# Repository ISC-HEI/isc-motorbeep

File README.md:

<picture>
  <source media="(prefers-color-scheme: dark)"
          srcset="https://raw.githubusercontent.com/ISC-HEI/isc-logos/main/white/ISC%20Logo%20inline%20white%20v3%20-%20large.webp">
  
</picture>

# ISC MotorBeep — ESP32 dual-stepper + audio board

A complete [KiCad 9](https://www.kicad.org/) schematic for an ESP32 board driving two bipolar
stepper motors and a small speaker, powered from 3× AA cells. It is an improved derivative of the
ESP32 DevKit DOIT v1: the AMS1117 LDO, the thin bulk capacitance, the micro-USB connector and the
absent battery sensing are all addressed.

## The brief

Take the [ESP32 DevKit DOIT v1](https://embedded-systems-design.github.io/overview-of-the-esp32-devkit-doit-v1/)
as the reference design and produce an improved version of it that drives **two stepper motors** and
a **small speaker**, running off **AA cells** — originally two, changed to three during the work.
Deliver the complete schematic in KiCad (installing it as needed), authored through the
[KiCAD-MCP-Server](https://github.com/mixelpixx/KiCAD-MCP-Server).

## What was built

1. KiCad 9 installed, the MCP server built, and patched — it emits the KiCad 10 file format, which 9 refuses to load.
2. Architecture chosen from the battery up: 3× AA (2.8–4.8 V) sits inside the STSPIN220 and MAX98357A supply windows, so motors and audio need no converter; only the ESP32 does, and it must be a buck-boost.
3. Parts picked against what KiCad actually ships — `DRV8834` and `TPS63020` have no stock symbols, so `STSPIN220` and `TPS63001` replaced them.
4. Four hierarchical sheets authored headlessly: power, MCU, motors, audio. **Root ERC: 0 errors.**
5. Verified three ways — ERC, a rendered image of every sheet reviewed by eye, and `check_nets.py`, which asserts 29 design-intent connections against the exported netlist.
6. Footprints assigned and checked to exist, netlist and PDF exported, BOM priced against the real JLCPCB catalog (**$14.49**, part links in [`doc/BOM.md`](./doc/BOM.md)).
7. A 4-layer PCB created and fully placed — antenna overhanging the edge, switching nodes 4.3 mm — then rendered in 3D. **Routing was not done.**

## Schematic

Four hierarchical sheets plus a root. Click any image for full resolution, or read
[the complete PDF](./doc/isc-motorbeep-schematic.pdf).

### Root — sheet hierarchy

### Power — 3× AA, Schottky OR, TPS63001 buck-boost, USB-C

### MCU — ESP32-WROOM-32E, CP2102N bridge, auto-reset

### Motors — 2× STSPIN220 stepper drivers

### Audio — MAX98357A Class-D

## PCB

Placed, not routed. 70 x 50 mm, 4 layers, 69 footprints, verified by
[`tools/place_board.py`](./tools/place_board.py): no overlaps, nothing off-board, and nothing
inside the ESP32 antenna keepout. The module's antenna deliberately overhangs the top edge, and
L1 sits directly left of the TPS63001 so both switching nodes come out as 4.3 mm straight runs.

Routing is not done, so there are no tracks and no copper pours yet.

## Architecture

Three AA cells deliver 2.8–4.8 V, and that range sits inside the supply window of both power loads —
the STSPIN220 works from 1.8 V and the MAX98357A from 2.5 V — so the motors and the speaker run
straight off the pack with no converter at all. Only the ESP32 needs one, and it has to be a
buck-boost: the pack starts above 3.3 V and ends below it, so an LDO would drop out and a plain
boost could not regulate down. USB and battery are OR'd through two Schottky diodes into that
converter only, which is what stops USB from back-feeding and charging the alkaline cells.

```mermaid
flowchart LR
    B["3x AA / 2.8-4.8 V"] --> D2["D2 Schottky"]
    U["USB-C 5 V"] --> D1["D1 Schottky"]
    D1 --> V["VSYS"]
    D2 --> V
    V --> R["U2 TPS63001 buck-boost"]
    R --> L3["+3V3 - ESP32 only"]
    B --> M["U5/U6 STSPIN220 - 2 steppers"]
    B --> A["U7 MAX98357A - speaker"]
```

Every line the ESP32 gates has a resistor defining its state at reset, so the motors cannot twitch
and the speaker cannot pop at power-up; `GPIO12` is left unconnected because it straps the flash
voltage. The reasoning, the full pin budget and the pre-fabrication checklist are in
**[`doc/DESIGN.md`](./doc/DESIGN.md)**.

## Bill of materials

70 components in 36 lines, about **$14.49** in parts at 1-off LCSC prices (catalog snapshot of
14 September 2026). Full priced BOM with a part link per line: **[`doc/BOM.md`](./doc/BOM.md)**.

> [!WARNING]
> **The STSPIN220 was down to 27 units at JLCPCB in that snapshot** — check it live before
> committing to a build. `doc/BOM.md` names the substitute and what swapping costs you.

Almost every part is a JLCPCB *Extended* part with a $3 setup fee each, so for a one-off, hand
assembly is cheaper than paying the setup fees.

## Open it

```bash
kicad hardware/isc-motorbeep/isc-motorbeep.kicad_pro
```

Generated headlessly through the KiCAD-MCP-Server — reproduction steps, the KiCad 9 file-format
patch it needs, and the helper scripts are in [`doc/TOOLING.md`](./doc/TOOLING.md).

## Before fabricating

The schematic is complete and ERC-clean, but two questions could not be settled without
manufacturer datasheets. Both are detailed, with the rest of the checklist, in
[`doc/DESIGN.md` §8.5–8.6](./doc/DESIGN.md):

- **Are the STSPIN220 and MAX98357A logic inputs rated independently of their supply?** The ESP32
  drives 3.3 V into them while `+BATT` may be at 2.8 V. If either is VS-referenced, the design
  breaks at low battery. This is the one that matters.
- **The QFN-16 exposed-pad dimension** for U5/U6/U7 — stock footprint variants run 1.45 to 1.85 mm,
  and it is the thermal path the current-chopping depends on.

---

## License

Copyright © 2026 P.-A. Mudry / ISC — HES-SO Valais. Released under
[CC-BY-NC-ND 4.0](https://creativecommons.org/licenses/by-nc-nd/4.0/).

---

*Made with ♥ by mui, 2026*

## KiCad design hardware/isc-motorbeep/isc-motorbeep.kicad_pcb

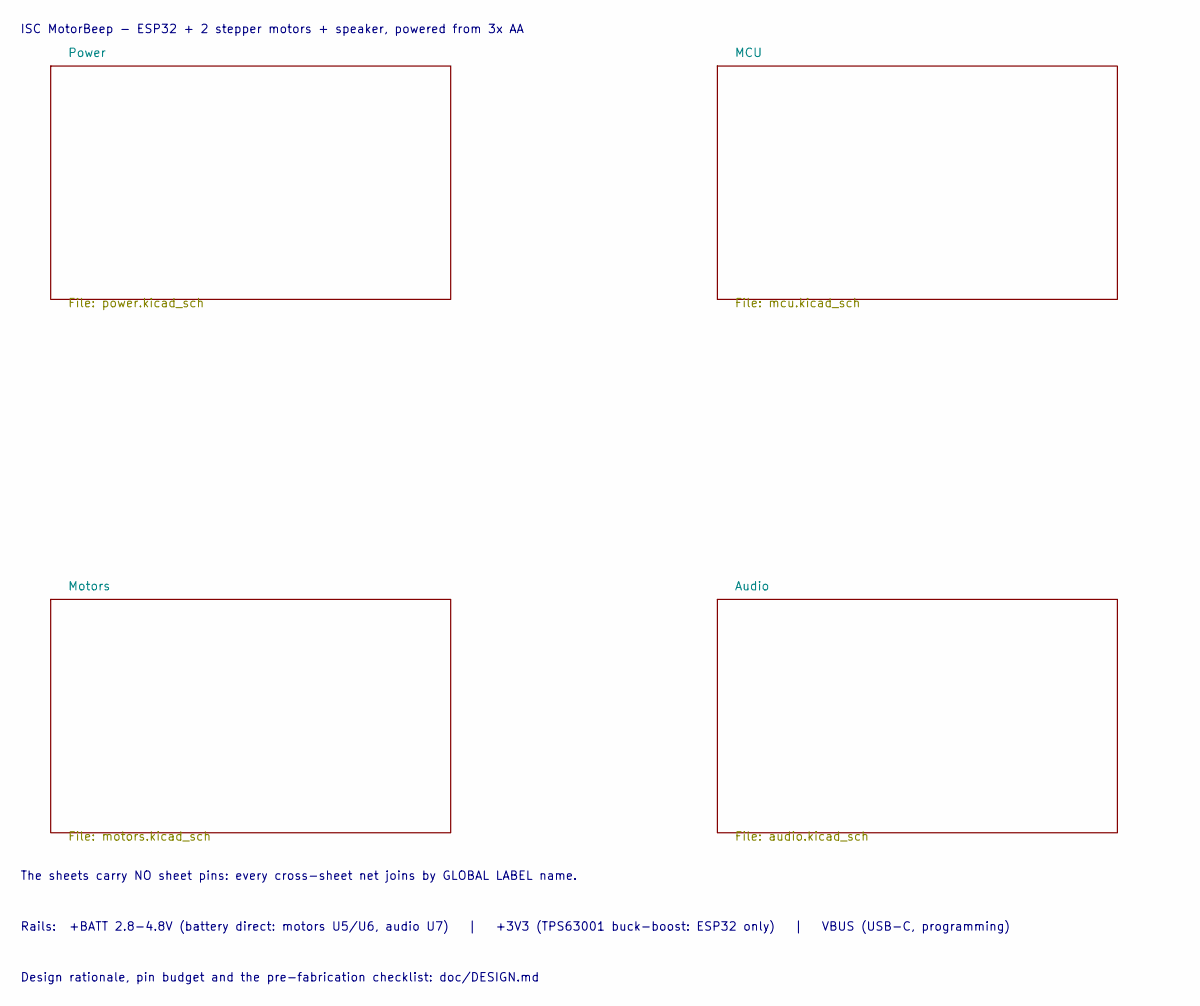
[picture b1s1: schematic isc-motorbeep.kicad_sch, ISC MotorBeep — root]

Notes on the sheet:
ISC MotorBeep - ESP32 + 2 stepper motors + speaker, powered from 3x AA
The sheets carry NO sheet pins: every cross-sheet net joins by GLOBAL LABEL name.
Rails: +BATT 2.8-4.8V (battery direct: motors U5/U6, audio U7) | +3V3 (TPS63001 buck-boost: ESP32 only) | VBUS (USB-C, programming)
Design rationale, pin budget and the pre-fabrication checklist: doc/DESIGN.md

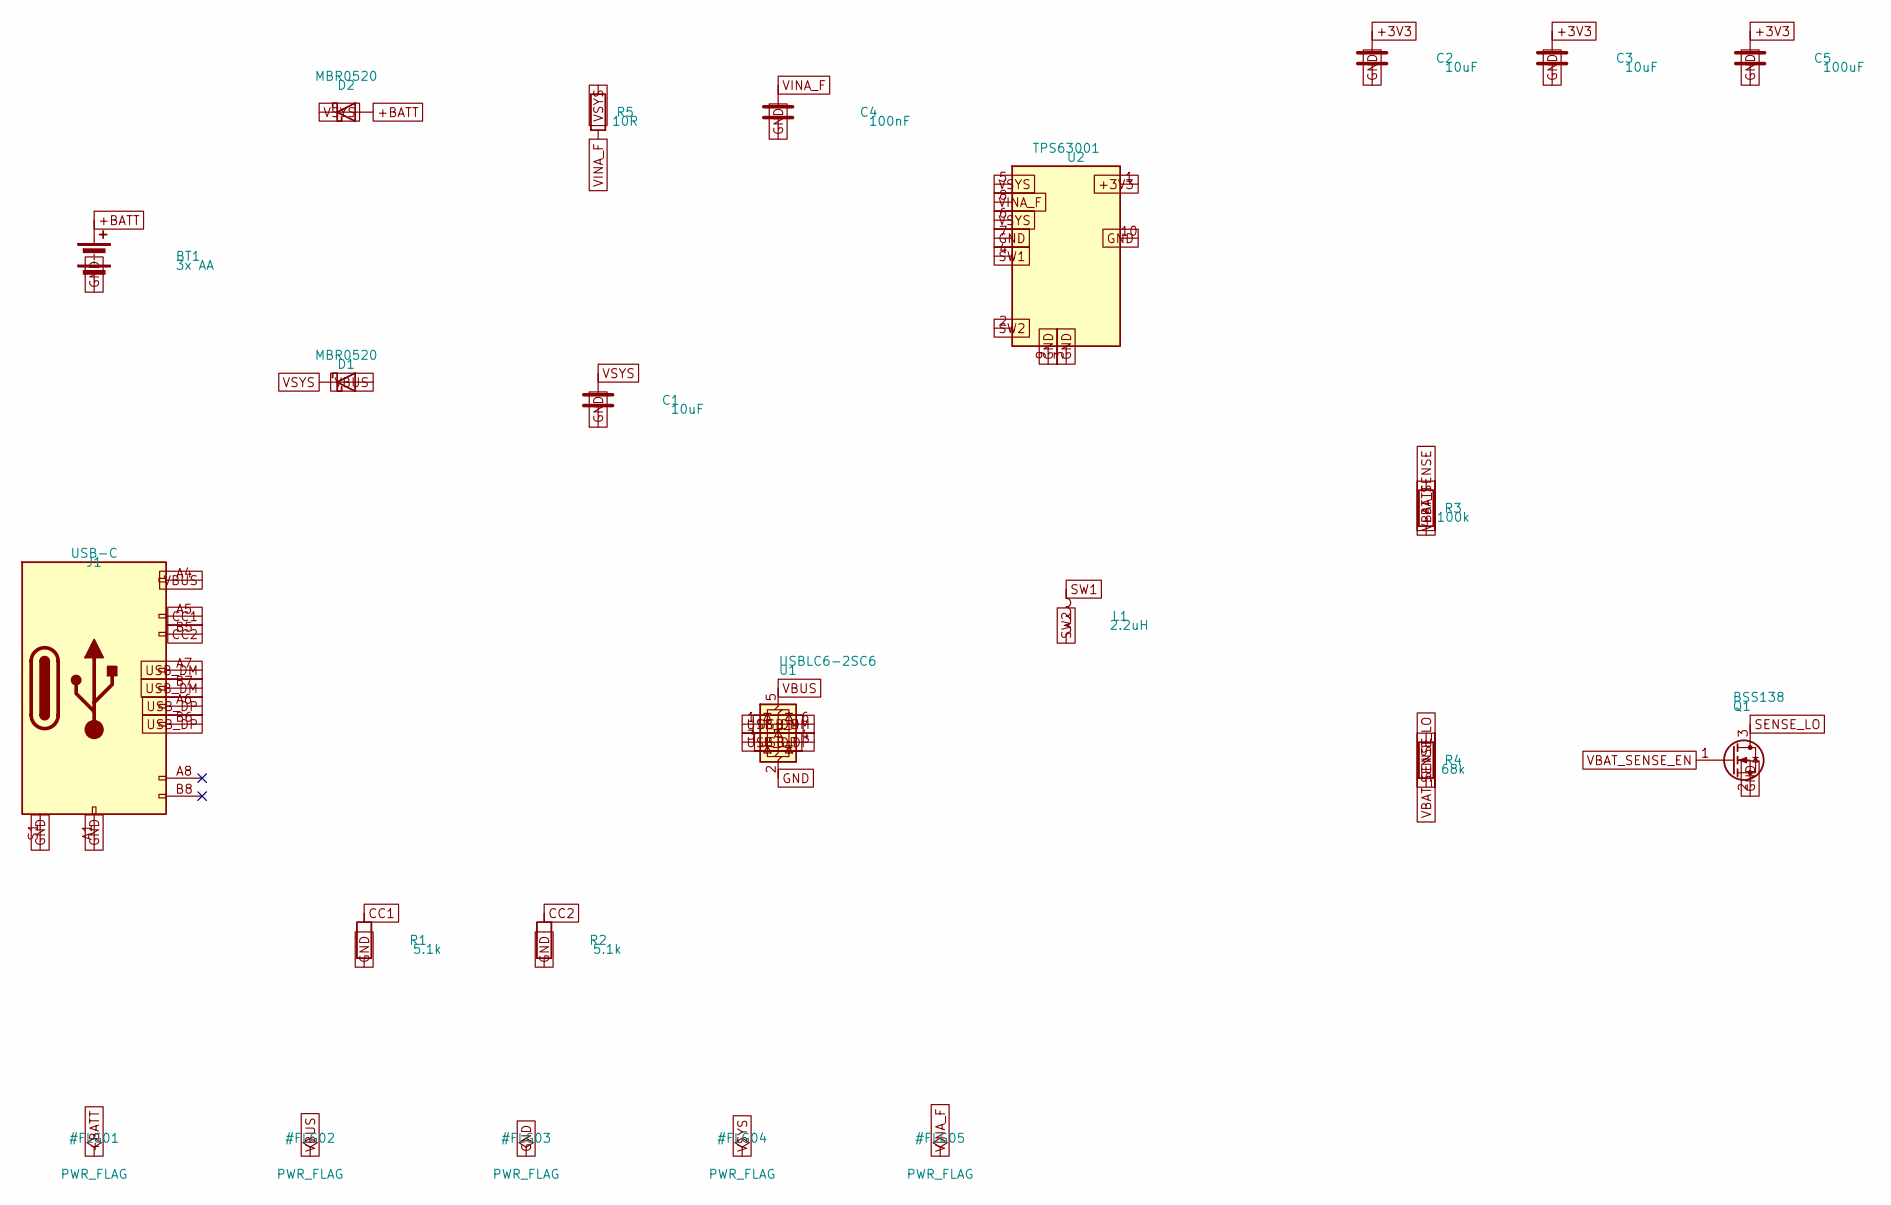
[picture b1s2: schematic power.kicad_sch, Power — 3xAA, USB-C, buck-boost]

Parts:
BT1: 3x AA; PinHeader_1x02_P2.54mm_Vertical
C1, C2, C3: 10uF; C_0805_2012Metric
C4: 100nF; C_0603_1608Metric
C5: 100uF; C_1210_3225Metric
D1, D2: MBR0520; D_SOD-123
J1: USB-C; USB_C_Receptacle_G-Switch_GT-USB-7010ASV
L1: 2.2uH; L_Bourns-SRN4018
Q1: BSS138; SOT-23
R1, R2: 5.1k; R_0603_1608Metric
R3: 100k; R_0603_1608Metric
R4: 68k; R_0603_1608Metric
R5: 10R; R_0603_1608Metric
U1: USBLC6-2SC6; SOT-23-6
U2: TPS63001; Texas_DRC0010J_ThermalVias

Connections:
+3V3: C2.1, C3.1, C5.1, U2.1 (VOUT); also elsewhere on the board
+BATT: BT1.1 (+), D2.2 (A), R3.1; also elsewhere on the board
CC1: J1.A5 (CC1), R1.1
CC2: J1.B5 (CC2), R2.1
GND: BT1.2 (-), C1.2, C2.2, C3.2, C4.2, C5.2, J1.A1 (GND), J1.A12 (GND), J1.B1 (GND), J1.B12 (GND), J1.S1 (SHIELD), Q1.2 (S), R1.2, R2.2, U1.2 (GND), U2.3 (PGND), U2.7 (PS/SYNC), U2.9 (GND), U2.10 (FB), U2.11 (PGND); also elsewhere on the board
SENSE_LO: Q1.3 (D), R4.2
SW1: L1.1, U2.4 (L1)
SW2: L1.2, U2.2 (L2)
USB_DM: J1.A7 (D-), J1.B7 (D-), U1.1 (I/O1), U1.6 (I/O1); also elsewhere on the board
USB_DP: J1.A6 (D+), J1.B6 (D+), U1.3 (I/O2), U1.4 (I/O2); also elsewhere on the board
VBAT_SENSE: R3.2, R4.1; also elsewhere on the board
VBAT_SENSE_EN: Q1.1 (G); also elsewhere on the board
VBUS: D1.2 (A), J1.A4 (VBUS), J1.A9 (VBUS), J1.B4 (VBUS), J1.B9 (VBUS), U1.5 (VBUS); also elsewhere on the board
VINA_F: C4.1, R5.2, U2.8 (VINA)
VSYS: C1.1, D1.1 (K), D2.1 (K), R5.1, U2.5 (VIN), U2.6 (EN)

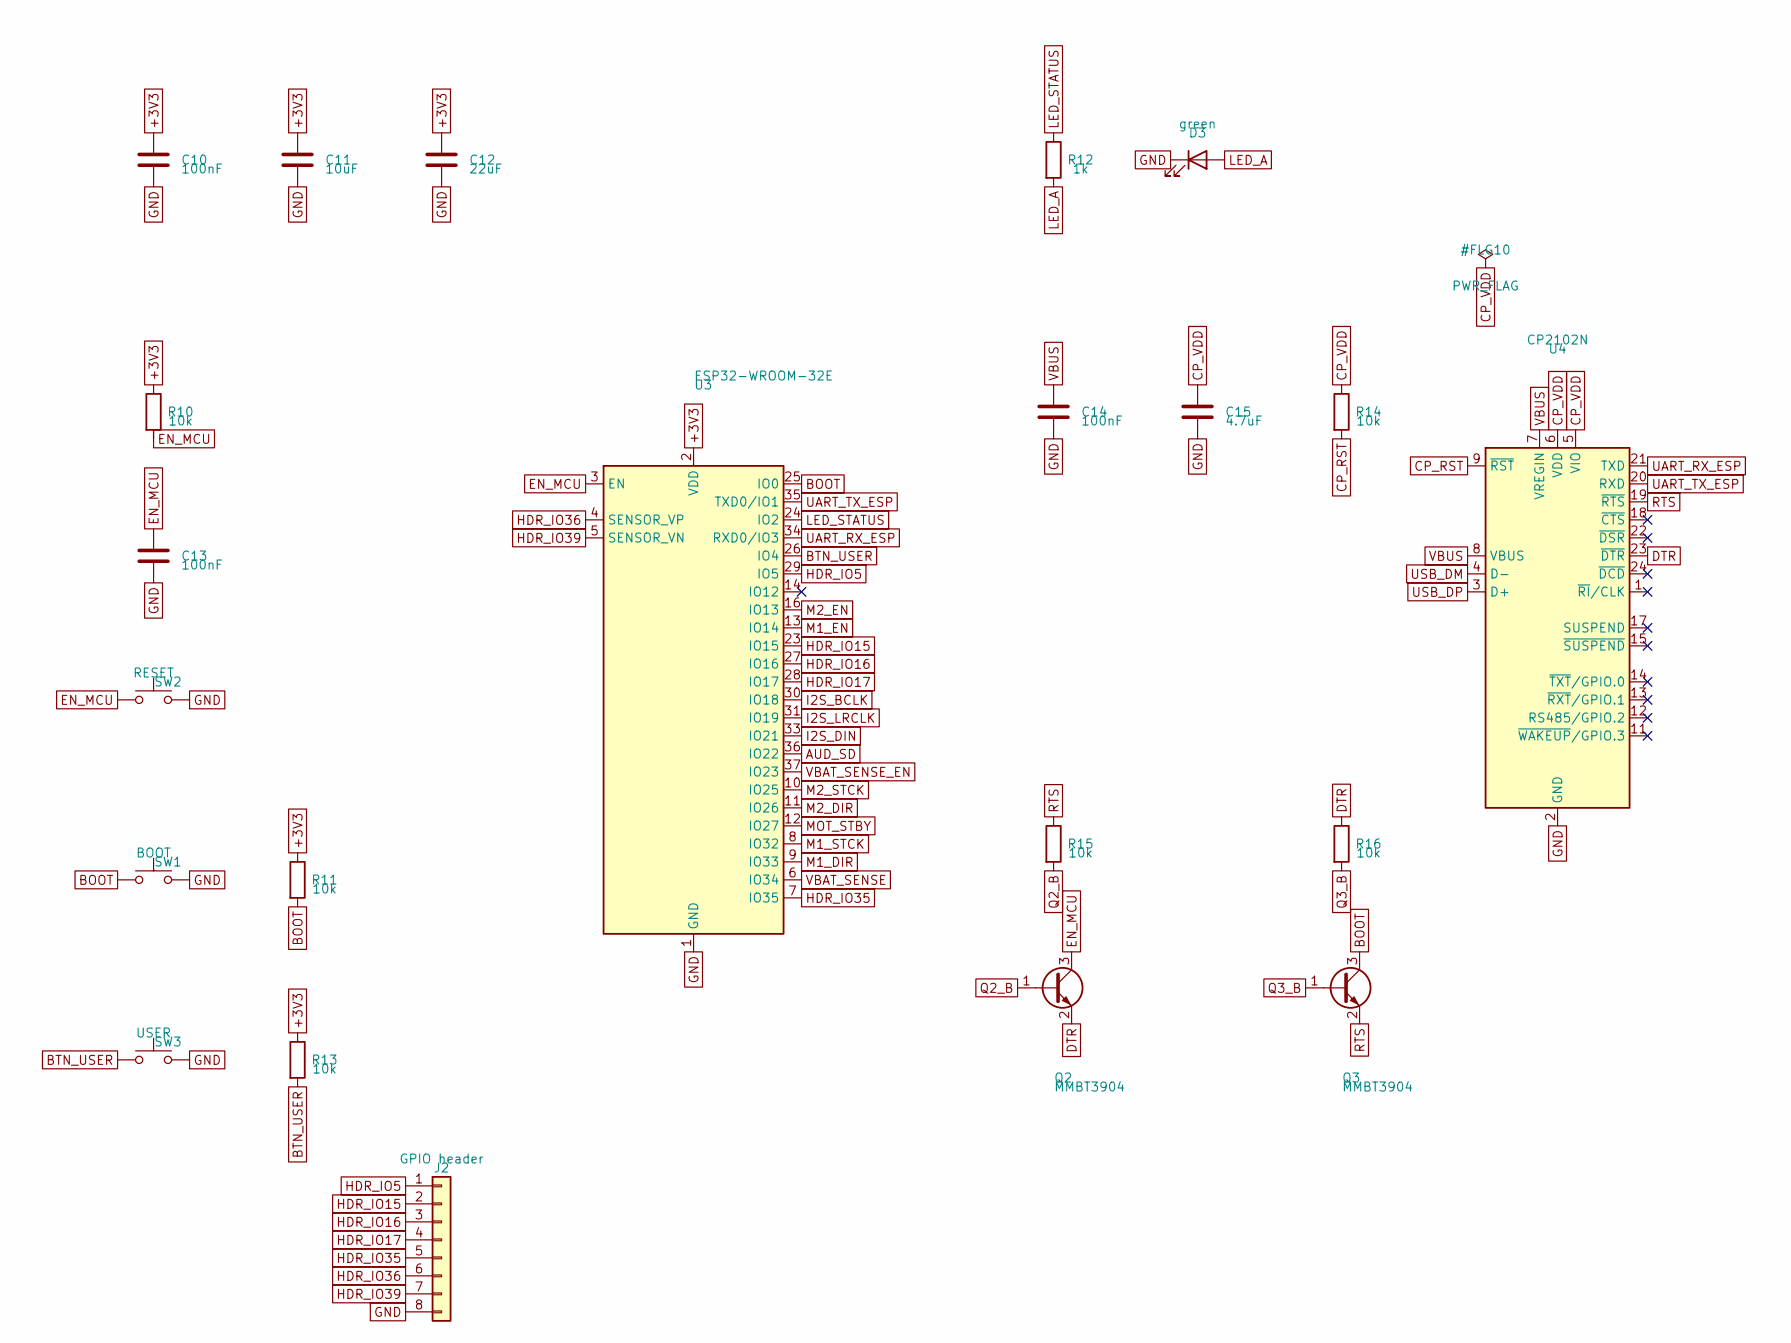
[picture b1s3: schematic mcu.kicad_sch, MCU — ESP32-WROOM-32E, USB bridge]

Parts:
C10, C13, C14: 100nF; C_0603_1608Metric
C11: 10uF; C_0805_2012Metric
C12: 22uF; C_0805_2012Metric
C15: 4.7uF; C_0805_2012Metric
D3: green; LED_0603_1608Metric
J2: GPIO header; PinHeader_1x08_P2.54mm_Vertical
Q2, Q3: MMBT3904; SOT-23
R10, R11, R13, R14, R15, R16: 10k; R_0603_1608Metric
R12: 1k; R_0603_1608Metric
SW1: BOOT; SW_SPST_SKQG_WithoutStem
SW2: RESET; SW_SPST_SKQG_WithoutStem
SW3: USER; SW_SPST_SKQG_WithoutStem
U3: ESP32-WROOM-32E
U4: CP2102N; QFN-24-1EP_4x4mm_P0.5mm_EP2.15x2.15mm

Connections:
+3V3: C10.1, C11.1, C12.1, R10.1, R11.1, R13.1, U3.2 (VDD); also elsewhere on the board
AUD_SD: U3.36 (IO22); also elsewhere on the board
BOOT: Q3.3 (C), R11.2, SW1.1, U3.25 (IO0)
BTN_USER: R13.2, SW3.1, U3.26 (IO4)
CP_RST: R14.2, U4.9 (~RST)
CP_VDD: C15.1, R14.1, U4.5 (VIO), U4.6 (VDD)
DTR: Q2.2 (E), R16.1, U4.23 (~DTR)
EN_MCU: C13.1, Q2.3 (C), R10.2, SW2.1, U3.3 (EN)
GND: C10.2, C11.2, C12.2, C13.2, C14.2, C15.2, D3.1 (K), J2.8, SW1.2, SW2.2, SW3.2, U3.1 (GND), U3.15 (GND), U3.38 (GND), U3.39 (GND), U4.2 (GND), U4.25 (GND); also elsewhere on the board
HDR_IO5: J2.1, U3.29 (IO5)
HDR_IO15: J2.2, U3.23 (IO15)
HDR_IO16: J2.3, U3.27 (IO16)
HDR_IO17: J2.4, U3.28 (IO17)
HDR_IO35: J2.5, U3.7 (IO35)
HDR_IO36: J2.6, U3.4 (SENSOR_VP)
HDR_IO39: J2.7, U3.5 (SENSOR_VN)
I2S_BCLK: U3.30 (IO18); also elsewhere on the board
I2S_DIN: U3.33 (IO21); also elsewhere on the board
I2S_LRCLK: U3.31 (IO19); also elsewhere on the board
LED_A: D3.2 (A), R12.2
LED_STATUS: R12.1, U3.24 (IO2)
M1_DIR: U3.9 (IO33); also elsewhere on the board
M1_EN: U3.13 (IO14); also elsewhere on the board
M1_STCK: U3.8 (IO32); also elsewhere on the board
M2_DIR: U3.11 (IO26); also elsewhere on the board
M2_EN: U3.16 (IO13); also elsewhere on the board
M2_STCK: U3.10 (IO25); also elsewhere on the board
MOT_STBY: U3.12 (IO27); also elsewhere on the board
Q2_B: Q2.1 (B), R15.2
Q3_B: Q3.1 (B), R16.2
RTS: Q3.2 (E), R15.1, U4.19 (~RTS)
UART_RX_ESP: U3.34 (RXD0/IO3), U4.21 (TXD)
UART_TX_ESP: U3.35 (TXD0/IO1), U4.20 (RXD)
USB_DM: U4.4 (D-); also elsewhere on the board
USB_DP: U4.3 (D+); also elsewhere on the board
VBAT_SENSE: U3.6 (IO34); also elsewhere on the board
VBAT_SENSE_EN: U3.37 (IO23); also elsewhere on the board
VBUS: C14.1, U4.7 (VREGIN), U4.8 (VBUS); also elsewhere on the board

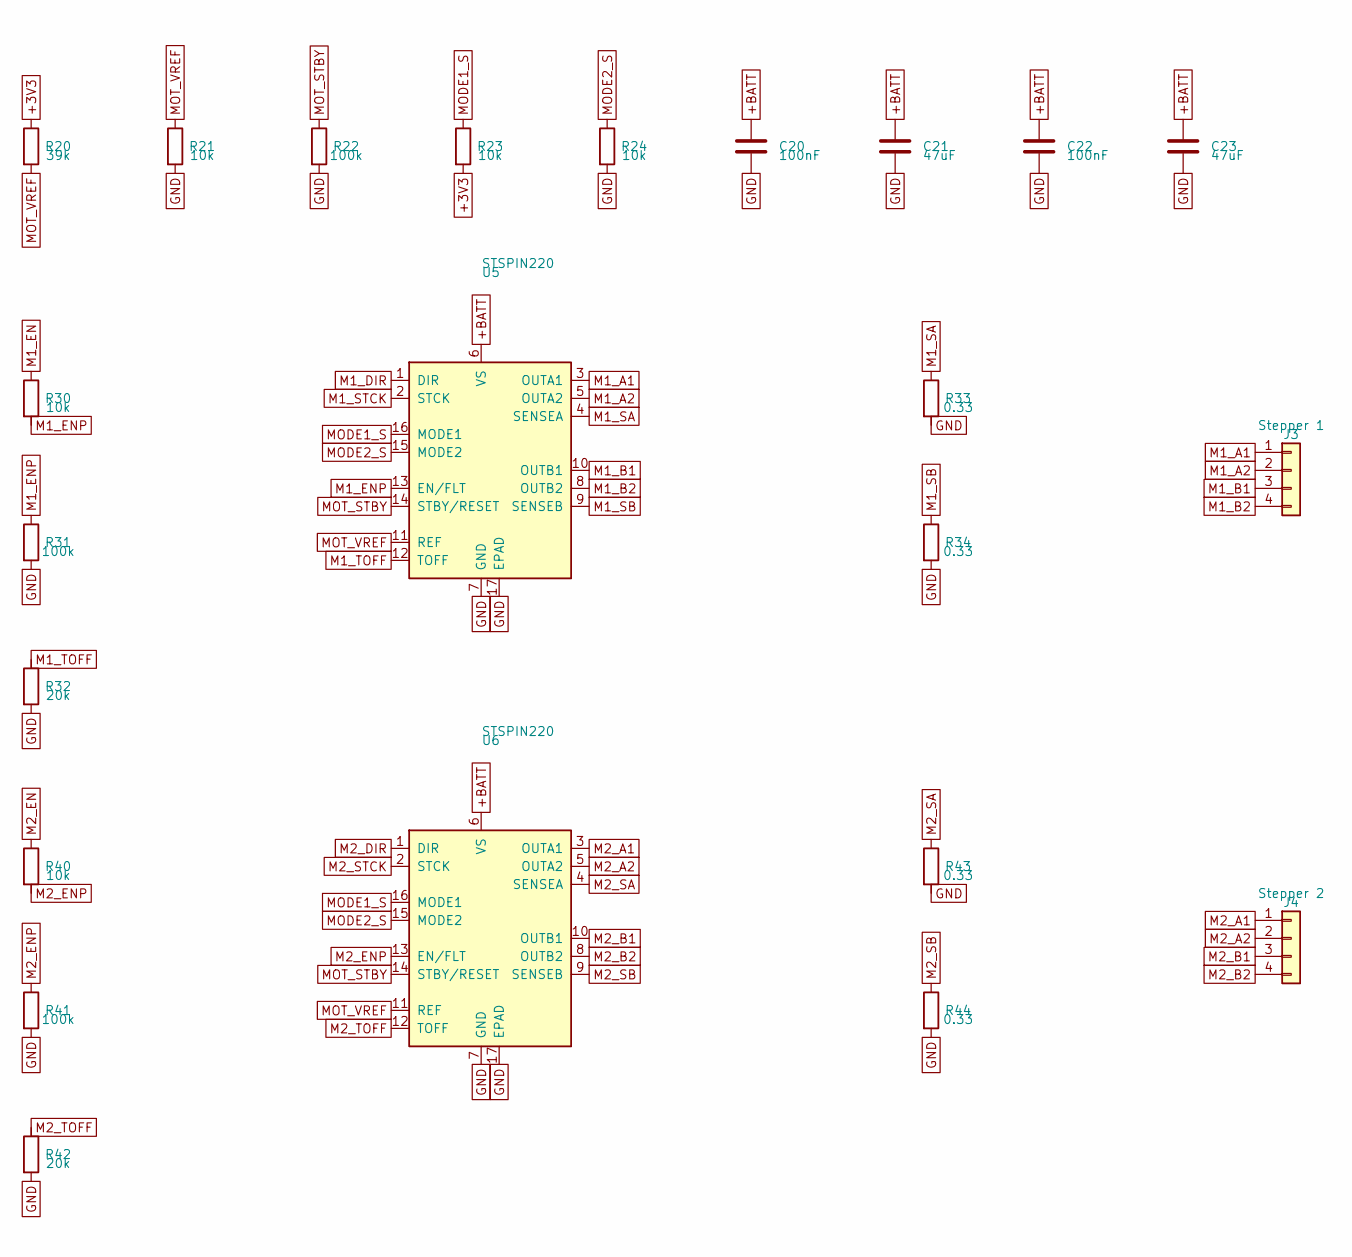
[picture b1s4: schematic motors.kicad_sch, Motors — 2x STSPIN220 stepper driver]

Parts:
C20, C22: 100nF; C_0603_1608Metric
C21, C23: 47uF; C_1210_3225Metric
J3: Stepper 1; PinHeader_1x04_P2.54mm_Vertical
J4: Stepper 2; PinHeader_1x04_P2.54mm_Vertical
R20: 39k; R_0603_1608Metric
R21, R23, R24, R30, R40: 10k; R_0603_1608Metric
R22, R31, R41: 100k; R_0603_1608Metric
R32, R42: 20k; R_0603_1608Metric
R33, R34, R43, R44: 0.33; R_1206_3216Metric
U5, U6: STSPIN220; QFN-16-1EP_3x3mm_P0.5mm_EP1.45x1.45mm_ThermalVias

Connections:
+3V3: R20.1, R23.2; also elsewhere on the board
+BATT: C20.1, C21.1, C22.1, C23.1, U5.6 (VS), U6.6 (VS); also elsewhere on the board
GND: C20.2, C21.2, C22.2, C23.2, R21.2, R22.2, R24.2, R31.2, R32.2, R33.2, R34.2, R41.2, R42.2, R43.2, R44.2, U5.7 (GND), U5.17 (EPAD), U6.7 (GND), U6.17 (EPAD); also elsewhere on the board
M1_A1: J3.1, U5.3 (OUTA1)
M1_A2: J3.2, U5.5 (OUTA2)
M1_B1: J3.3, U5.10 (OUTB1)
M1_B2: J3.4, U5.8 (OUTB2)
M1_DIR: U5.1 (DIR); also elsewhere on the board
M1_EN: R30.1; also elsewhere on the board
M1_ENP: R30.2, R31.1, U5.13 (EN/FLT)
M1_SA: R33.1, U5.4 (SENSEA)
M1_SB: R34.1, U5.9 (SENSEB)
M1_STCK: U5.2 (STCK); also elsewhere on the board
M1_TOFF: R32.1, U5.12 (TOFF)
M2_A1: J4.1, U6.3 (OUTA1)
M2_A2: J4.2, U6.5 (OUTA2)
M2_B1: J4.3, U6.10 (OUTB1)
M2_B2: J4.4, U6.8 (OUTB2)
M2_DIR: U6.1 (DIR); also elsewhere on the board
M2_EN: R40.1; also elsewhere on the board
M2_ENP: R40.2, R41.1, U6.13 (EN/FLT)
M2_SA: R43.1, U6.4 (SENSEA)
M2_SB: R44.1, U6.9 (SENSEB)
M2_STCK: U6.2 (STCK); also elsewhere on the board
M2_TOFF: R42.1, U6.12 (TOFF)
MODE1_S: R23.1, U5.16 (MODE1), U6.16 (MODE1)
MODE2_S: R24.1, U5.15 (MODE2), U6.15 (MODE2)
MOT_STBY: R22.1, U5.14 (STBY/RESET), U6.14 (STBY/RESET); also elsewhere on the board
MOT_VREF: R20.2, R21.1, U5.11 (REF), U6.11 (REF)

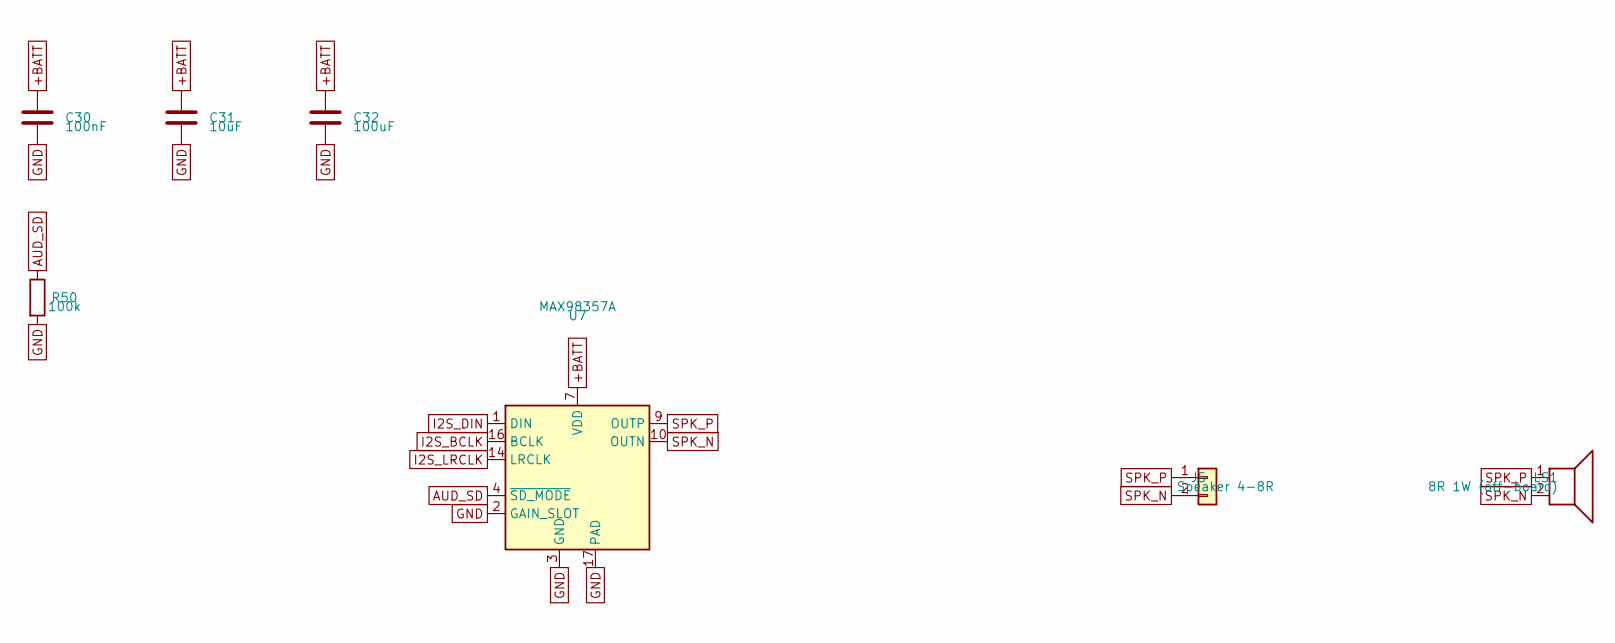
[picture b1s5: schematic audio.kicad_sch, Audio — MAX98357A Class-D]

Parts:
C30: 100nF; C_0603_1608Metric
C31: 10uF; C_0805_2012Metric
C32: 100uF; C_1210_3225Metric
J5: Speaker 4-8R; PinHeader_1x02_P2.54mm_Vertical
LS1: 8R 1W (off-board)
R50: 100k; R_0603_1608Metric
U7: MAX98357A; QFN-16-1EP_3x3mm_P0.5mm_EP1.45x1.45mm_ThermalVias

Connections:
+BATT: C30.1, C31.1, C32.1, U7.7 (VDD), U7.8 (VDD); also elsewhere on the board
AUD_SD: R50.1, U7.4 (~SD_MODE); also elsewhere on the board
GND: C30.2, C31.2, C32.2, R50.2, U7.2 (GAIN_SLOT), U7.3 (GND), U7.11 (GND), U7.15 (GND), U7.17 (PAD); also elsewhere on the board
I2S_BCLK: U7.16 (BCLK); also elsewhere on the board
I2S_DIN: U7.1 (DIN); also elsewhere on the board
I2S_LRCLK: U7.14 (LRCLK); also elsewhere on the board
SPK_N: J5.2, LS1.2, U7.10 (OUTN)
SPK_P: J5.1, LS1.1, U7.9 (OUTP)

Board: 4 copper layers, 69 parts (0 on the bottom side), 67 nets, no tracks yet.

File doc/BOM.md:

# Bill of materials — ISC MotorBeep

Generated by `tools/price_bom.py` from the KiCAD-MCP-Server's offline JLCPCB
catalog. Prices are 1-off LCSC breaks and **move constantly** — re-run after a
`download_jlcpcb_database` to refresh. Each row links to its part page.

| Ref | Value | Package | LCSC | Qty | Unit $ | Line $ | Stock |
|---|---|---|---|---:|---:|---:|---:|
| `BT1` | 3x AA | PinHeader_1x02_P2.54mm_Vertical | [C115246](https://jlcpcb.com/partdetail/115246) | 1 | 0.2166 | **0.22** | 2,949 |
| `C1-C3,C11,C31` | 10uF | C_0805_2012Metric | [C109040](https://jlcpcb.com/partdetail/109040) | 5 | 0.1089 | **0.54** | 6,534 |
| `C4,C10,C13,C14,C20,C22,C30` | 100nF | C_0603_1608Metric | [C113803](https://jlcpcb.com/partdetail/113803) | 7 | 0.0129 | **0.09** | 22,292 |
| `C5,C32` | 100uF | C_1210_3225Metric | [C16196526](https://jlcpcb.com/partdetail/16196526) | 2 | 0.7412 | **1.48** | 1,323 |
| `C12` | 22uF | C_0805_2012Metric | [C128856](https://jlcpcb.com/partdetail/128856) | 1 | 0.0928 | **0.09** | 20,058 |
| `C15` | 4.7uF | C_0805_2012Metric | [C106839](https://jlcpcb.com/partdetail/106839) | 1 | 0.0479 | **0.05** | 1,067 |
| `C21,C23` | 47uF | C_1210_3225Metric | [C16196538](https://jlcpcb.com/partdetail/16196538) | 2 | 0.2780 | **0.56** | 961 |
| `D1,D2` | MBR0520 | D_SOD-123 | [C22378360](https://jlcpcb.com/partdetail/22378360) | 2 | 0.0146 | **0.03** | 10,217 |
| `D3` | green | LED_0603_1608Metric | [C125102](https://jlcpcb.com/partdetail/125102) | 1 | 0.0166 | **0.02** | 109,618 |
| `J1` | USB-C | USB_C_Receptacle_G-Switch_GT-USB-7010ASV | [C165948](https://jlcpcb.com/partdetail/165948) | 1 | 0.1858 | **0.19** | 89,797 |
| `J2` | GPIO header | PinHeader_1x08_P2.54mm_Vertical | [C115246](https://jlcpcb.com/partdetail/115246) | 1 | — | *(same strip)* | 2,949 |
| `J3` | Stepper 1 | PinHeader_1x04_P2.54mm_Vertical | [C115246](https://jlcpcb.com/partdetail/115246) | 1 | — | *(same strip)* | 2,949 |
| `J4` | Stepper 2 | PinHeader_1x04_P2.54mm_Vertical | [C115246](https://jlcpcb.com/partdetail/115246) | 1 | — | *(same strip)* | 2,949 |
| `J5` | Speaker 4-8R | PinHeader_1x02_P2.54mm_Vertical | [C115246](https://jlcpcb.com/partdetail/115246) | 1 | — | *(same strip)* | 2,949 |
| `L1` | 2.2uH | L_Bourns-SRN4018 | [C107565](https://jlcpcb.com/partdetail/107565) | 1 | 0.0798 | **0.08** | 1,102 |
| `LS1` | 8R 1W (off-board) | — | — | 1 | — | — | — |
| `Q1` | BSS138 | SOT-23 | [C112239](https://jlcpcb.com/partdetail/112239) | 1 | 0.0176 | **0.02** | 271,091 |
| `Q2,Q3` | MMBT3904 | SOT-23 | [C22368849](https://jlcpcb.com/partdetail/22368849) | 2 | 0.0064 | **0.01** | 606 |
| `R1,R2` | 5.1k | R_0603_1608Metric | [C105580](https://jlcpcb.com/partdetail/105580) | 2 | 0.0020 | **0.00** | 5,622 |
| `R3,R22,R31,R41,R50` | 100k | R_0603_1608Metric | [C103200](https://jlcpcb.com/partdetail/103200) | 5 | 0.0014 | **0.01** | 517 |
| `R4` | 68k | R_0603_1608Metric | [C103818](https://jlcpcb.com/partdetail/103818) | 1 | 0.0010 | **0.00** | 725 |
| `R5` | 10R | R_0603_1608Metric | [C4297800](https://jlcpcb.com/partdetail/4297800) | 1 | 0.0026 | **0.00** | 5,241 |
| `R10,R11,R13-R16,R21,R23,R24,R30,R40` | 10k | R_0603_1608Metric | [C130232](https://jlcpcb.com/partdetail/130232) | 11 | 0.0038 | **0.04** | 1,192 |
| `R12` | 1k | R_0603_1608Metric | [C100835](https://jlcpcb.com/partdetail/100835) | 1 | 0.0012 | **0.00** | 2,564 |
| `R20` | 39k | R_0603_1608Metric | [C118370](https://jlcpcb.com/partdetail/118370) | 1 | 0.0006 | **0.00** | 4,415 |
| `R32,R42` | 20k | R_0603_1608Metric | [C101298](https://jlcpcb.com/partdetail/101298) | 2 | 0.0012 | **0.00** | 1,157 |
| `R33,R34,R43,R44` | 0.33 | R_1206_3216Metric | [C104942](https://jlcpcb.com/partdetail/104942) | 4 | 0.0079 | **0.03** | 4,803 |
| `SW1` | BOOT | SW_SPST_SKQG_WithoutStem | [C10852](https://jlcpcb.com/partdetail/10852) | 1 | 0.0225 | **0.02** | 892 |
| `SW2` | RESET | SW_SPST_SKQG_WithoutStem | [C10852](https://jlcpcb.com/partdetail/10852) | 1 | 0.0225 | **0.02** | 892 |
| `SW3` | USER | SW_SPST_SKQG_WithoutStem | [C10852](https://jlcpcb.com/partdetail/10852) | 1 | 0.0225 | **0.02** | 892 |
| `U1` | USBLC6-2SC6 | SOT-23-6 | [C47147619](https://jlcpcb.com/partdetail/47147619) | 1 | 0.0323 | **0.03** | 6,309 |
| `U2` | TPS63001 | Texas_DRC0010J_ThermalVias | [C28060](https://jlcpcb.com/partdetail/28060) | 1 | 1.7929 | **1.79** | 6,715 |
| `U3` | ESP32-WROOM-32E | ESP32-WROOM-32E | [C701341](https://jlcpcb.com/partdetail/701341) | 1 | 3.8183 | **3.82** | 20,082 |
| `U4` | CP2102N | QFN-24-1EP_4x4mm_P0.5mm_EP2.15x2.15mm | [C964632](https://jlcpcb.com/partdetail/964632) | 1 | 1.8059 | **1.81** | 14,927 |
| `U5,U6` | STSPIN220 | QFN-16-1EP_3x3mm_P0.5mm_EP1.45x1.45mm_ThermalVias | [C2150516](https://jlcpcb.com/partdetail/2150516) | 2 | 1.5033 | **3.01** | 27 |
| `U7` | MAX98357A | QFN-16-1EP_3x3mm_P0.5mm_EP1.45x1.45mm_ThermalVias | [C2682619](https://jlcpcb.com/partdetail/2682619) | 1 | 0.4995 | **0.50** | 16,467 |

**Total: $14.49 in parts for one board.**

## Notes

- `LS1` is the off-board speaker, deliberately unpriced — `J5` is the connector on the board.
- All five 2.54 mm headers are cut from one 1x40 strip (20 pins of 40), so the strip is counted once.
- Almost everything here is a JLCPCB *Extended* part, which carries a $3 setup fee each if you
  use their assembly service; for a one-off, hand assembly is cheaper than the setup fees.

## If the STSPIN220 is out of stock

It is the scarcest part in the design. The closest replacement is the **DRV8834**
(`C400392`, VQFN-24, or `C456273`, HTSSOP-24, ~$2.40). Its 2.5–10.8 V range still covers a
3x AA pack for its useful life, but it is not a drop-in: different footprint, and KiCad 9
ships no DRV8834 symbol, so the motors sheet would need a custom symbol and footprint.
